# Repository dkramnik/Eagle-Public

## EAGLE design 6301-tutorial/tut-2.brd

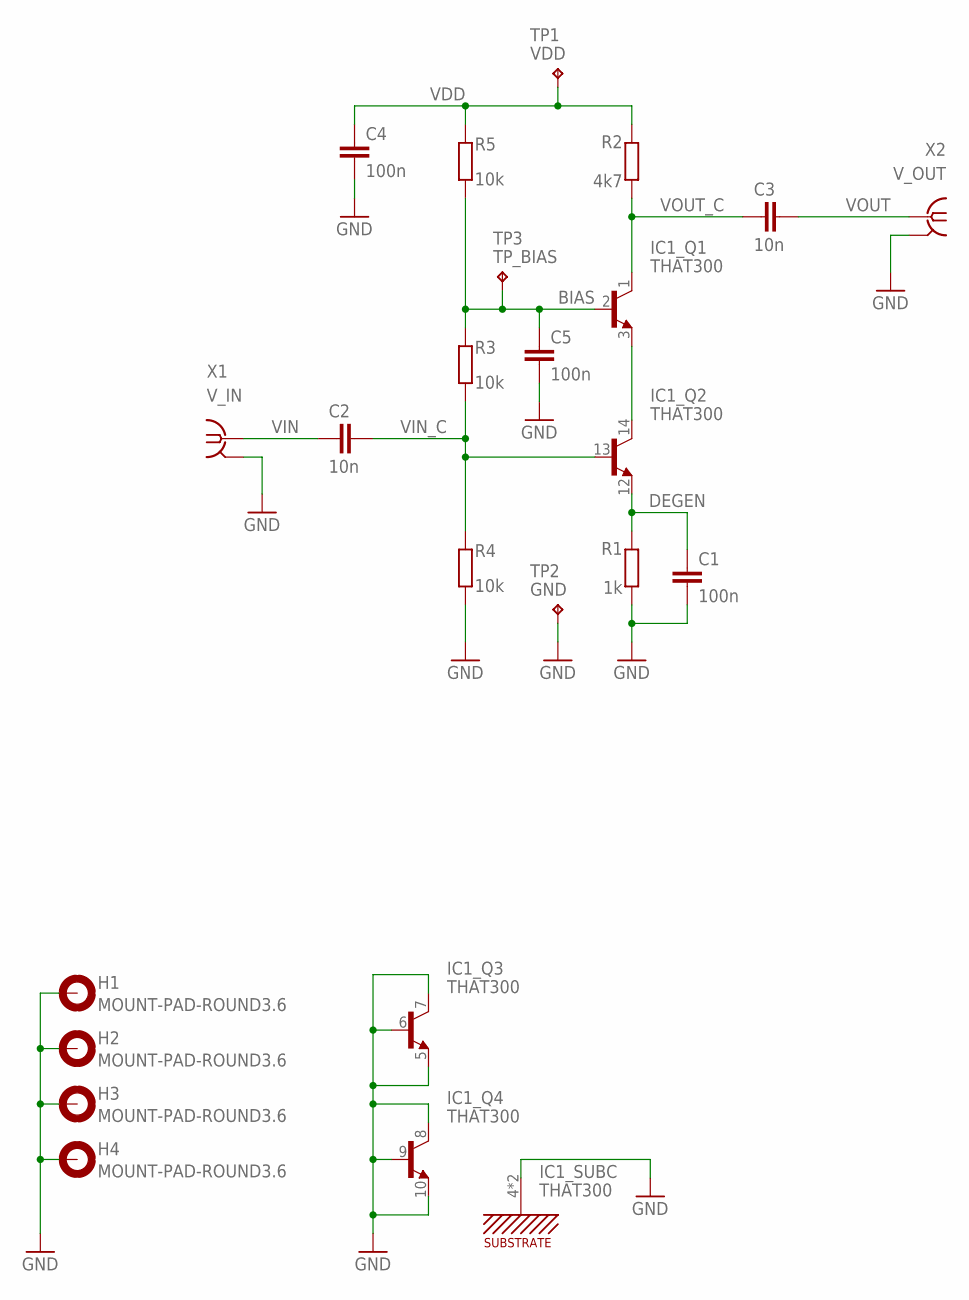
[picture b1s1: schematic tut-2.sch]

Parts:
C1, C4, C5: 100n; C050-025X075
C2, C3: 10n; C050-025X075
H1, H2, H3, H4: MOUNT-PAD-ROUND3.6; 3,6-PAD
IC1: THAT300; DIL14
R1: 1k; 0207/7
R2: 4k7; 0207/7
R3, R4, R5: 10k; 0207/7
TP1: VDD; KEYSTONE_5000_MINIATURE
TP2: GND; KEYSTONE_5000_MINIATURE
TP3: TP_BIAS; KEYSTONE_5000_MINIATURE
X1: V_IN; BU-SMA-H
X2: V_OUT; BU-SMA-H

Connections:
BIAS: C5.1, IC1.2 (B), R3.2, R5.1, TP3.P$1
DEGEN: C1.1, IC1.12 (E), R1.2
GND: C1.2, C4.2, C5.2, H1.B3,6, H2.B3,6, H3.B3,6, H4.B3,6, IC1.4 (SUBC), IC1.5 (E), IC1.6 (B), IC1.7 (C), IC1.8 (C), IC1.9 (B), IC1.10 (E), IC1.11 (SUBC), R1.1, R4.1, TP2.P$1, X1.2, X1.3 (2), X1.4 (2), X1.5 (2), X2.2, X2.3 (2), X2.4 (2), X2.5 (2)
unnamed: IC1.3 (E), IC1.14 (C)
VDD: C4.1, R2.2, R5.2, TP1.P$1
VIN: C2.1, X1.1
VIN_C: C2.2, IC1.13 (B), R3.1, R4.2
VOUT: C3.2, X2.1
VOUT_C: C3.1, IC1.1 (C), R2.1

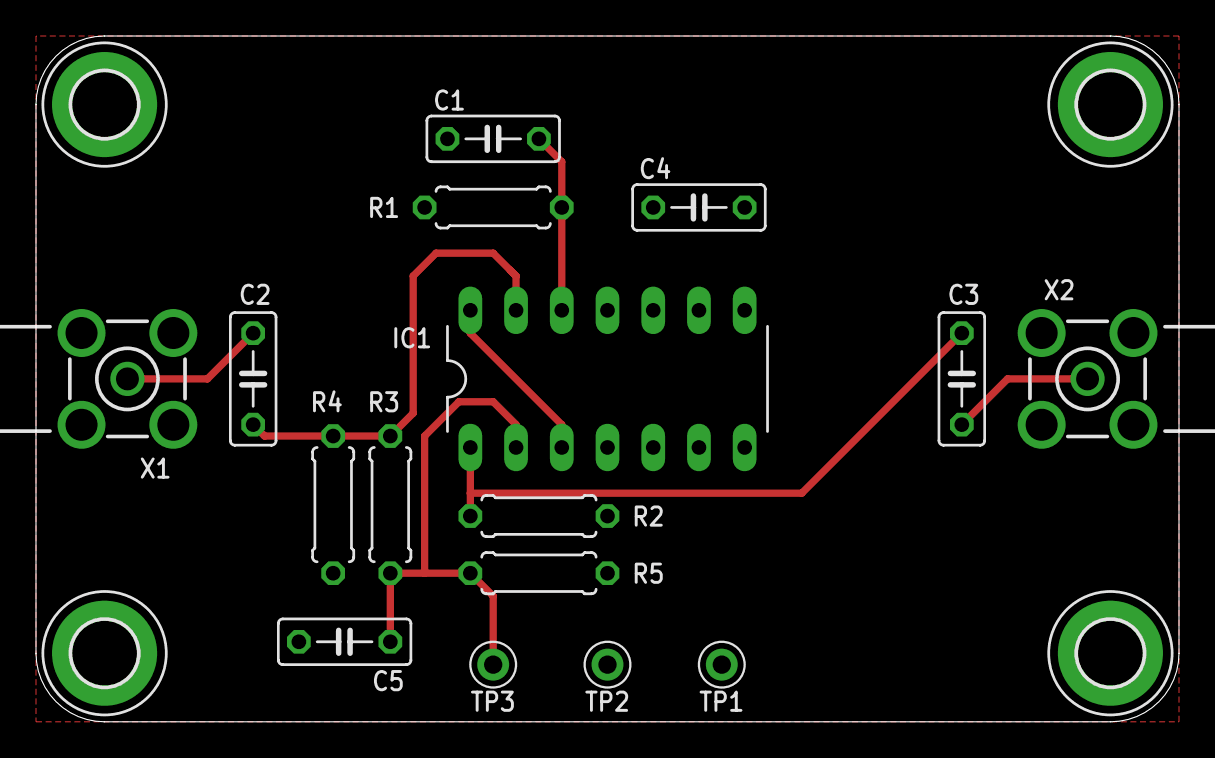
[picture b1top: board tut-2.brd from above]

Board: 2 copper layers, 63.5 x 38.1 mm, 20 parts (0 on the bottom side), 9 nets.

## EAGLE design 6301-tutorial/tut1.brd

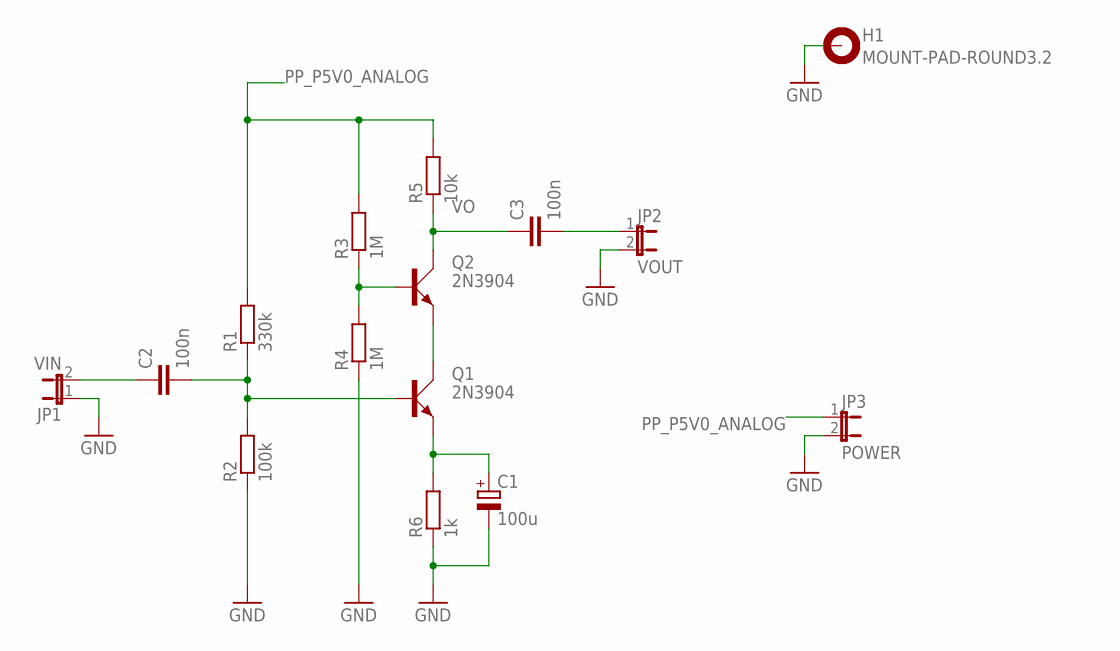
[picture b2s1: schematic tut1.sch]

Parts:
C1: 100u; E5-10,5
C2, C3: 100n; C050-025X075
H1: MOUNT-PAD-ROUND3.2; 3,2-PAD
JP1: VIN; JP1
JP2: VOUT; JP1
JP3: POWER; JP1
Q1, Q2: 2N3904; TO92D
R1: 330k; 0207/10
R2: 100k; 0207/10
R3, R4: 1M; 0207/10
R5: 10k; 0207/10
R6: 1k; 0207/10

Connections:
GND: C1.-, H1.B3,2, JP1.1, JP2.2, JP3.2, R2.1, R4.1, R6.1
unnamed: Q1.C, Q2.E
unnamed: C1.+, Q1.E, R6.2
unnamed: Q2.B, R3.1, R4.2
unnamed: C2.2, Q1.B, R1.1, R2.2
unnamed: C2.1, JP1.2
unnamed: C3.2, JP2.1
PP_P5V0_ANALOG: JP3.1, R1.2, R3.2, R5.2
VO: C3.1, Q2.C, R5.1

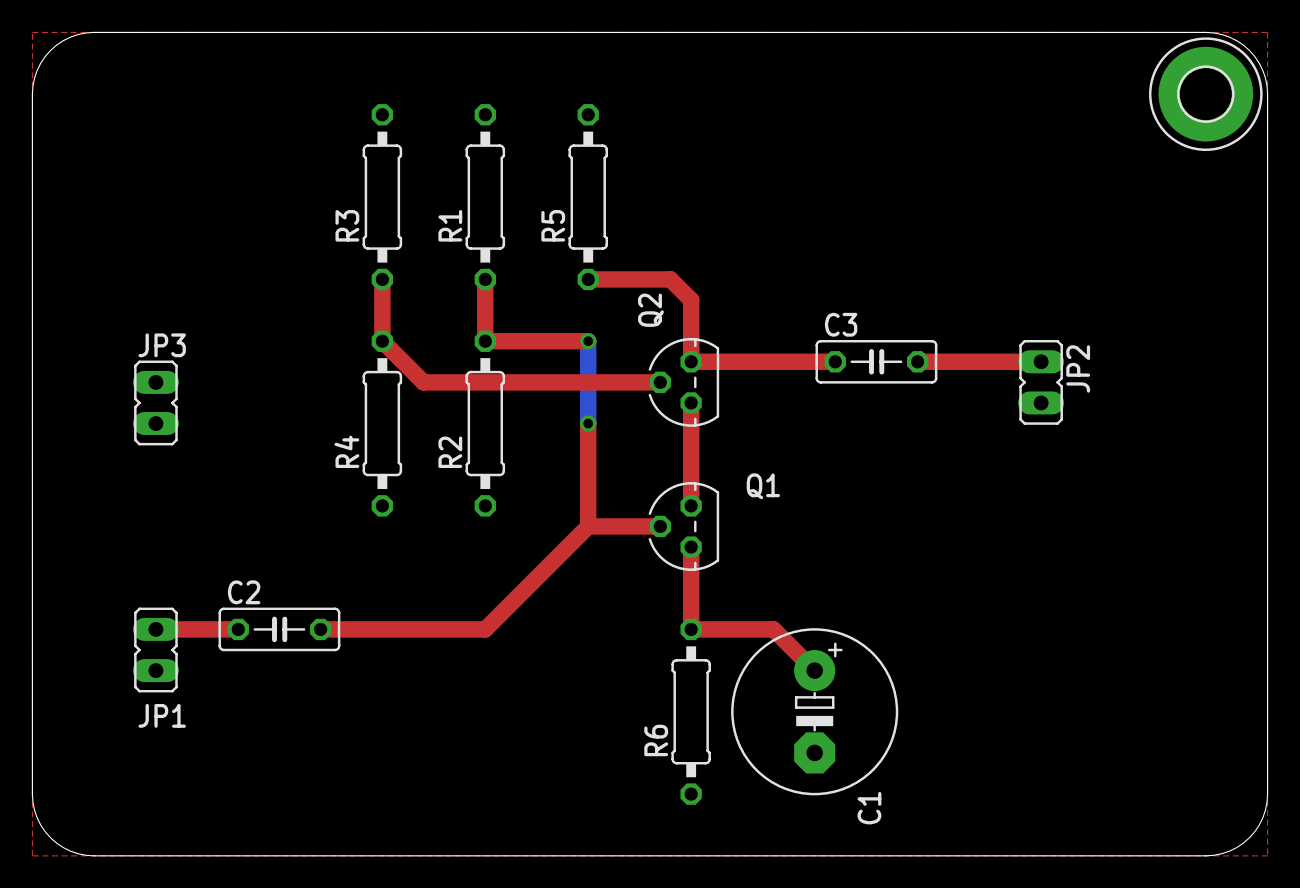
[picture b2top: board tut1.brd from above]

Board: 2 copper layers, 76.2 x 50.8 mm, 15 parts (0 on the bottom side), 9 nets.

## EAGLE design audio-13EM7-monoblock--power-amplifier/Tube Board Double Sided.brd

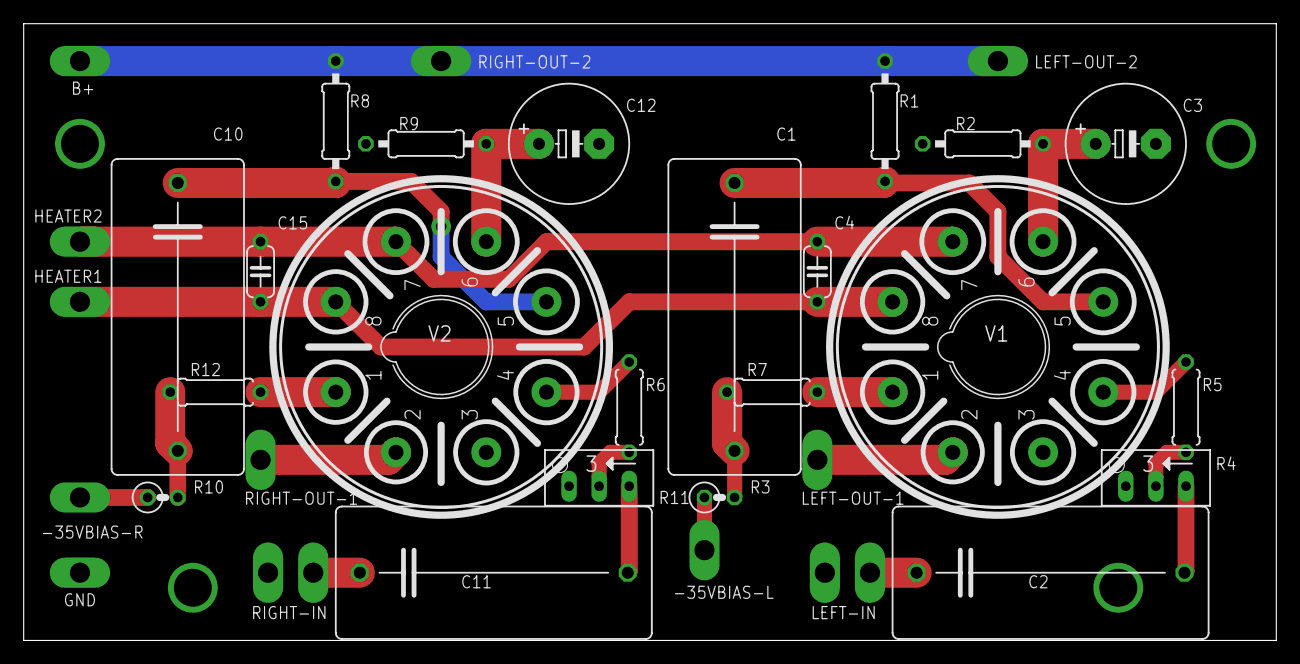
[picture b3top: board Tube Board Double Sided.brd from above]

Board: 2 copper layers, 105.7 x 52.0 mm, 34 parts (0 on the bottom side), 24 nets.

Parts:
-35VBIAS-L, -35VBIAS-R: PTR1PAD1-17Y; P1-17Y
B+: PTR1PAD1-17Y; P1-17Y
C1, C10: 0.015uF; C225-113X268
C2, C11: 0.1uF; C225-113X268
C3, C12: 100uF; E5-10,5
C4, C15: 1uF; C050-024X044
GND: PTR1PAD1-17Y; P1-17Y
HEATER1, HEATER2: PTR1PAD1-17Y; P1-17Y
LEFT-IN: PTR2; P2-38-17
LEFT-OUT-1, LEFT-OUT-2: PTR1PAD1-17Y; P1-17Y
R1, R8: 47K; 0207/10
R2, R9: 820R; 0207/10
R3, R10: 470K; 0207/2V
R4, R11: 100K; RJ9W
R5, R6: 33K; 0207/7
R7, R12: 2K2; 0207/7
RIGHT-IN: PTR2; P2-38-17
RIGHT-OUT-1, RIGHT-OUT-2: PTR1PAD1-17Y; P1-17Y
V1, V2: 13EM7; OKTAL

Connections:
B+: B+.TP, LEFT-OUT-2.TP, R1.2, R8.2, RIGHT-OUT-2.TP
GND: C3.-, C12.-, GND.TP, LEFT-IN.TP-2, R2.1, R4.A, R9.1, R11.A, RIGHT-IN.TP-2, V1.3, V2.3
HEATER: C4.1, C15.1, HEATER1.TP, V1.8, V2.8
unnamed: C4.2, C15.2, HEATER2.TP, V1.7, V2.7
unnamed: -35VBIAS-R.TP, R10.1
unnamed: R5.1, V1.4
unnamed: C1.1, R1.1, V1.5
unnamed: C3.+, R2.2, V1.6
unnamed: C1.2, R3.2, R7.2
unnamed: C2.2, R4.E
unnamed: R4.S, R5.2
unnamed: C2.1, LEFT-IN.TP-1
unnamed: C10.1, R8.1, V2.5
unnamed: LEFT-OUT-1.TP, V1.2
unnamed: R6.1, V2.4
unnamed: -35VBIAS-L.TP, R3.1
unnamed: R6.2, R11.S
unnamed: R7.1, V1.1
unnamed: C12.+, R9.2, V2.6
unnamed: C10.2, R10.2, R12.2
unnamed: C11.2, R11.E
unnamed: R12.1, V2.1
unnamed: C11.1, RIGHT-IN.TP-1
unnamed: RIGHT-OUT-1.TP, V2.2

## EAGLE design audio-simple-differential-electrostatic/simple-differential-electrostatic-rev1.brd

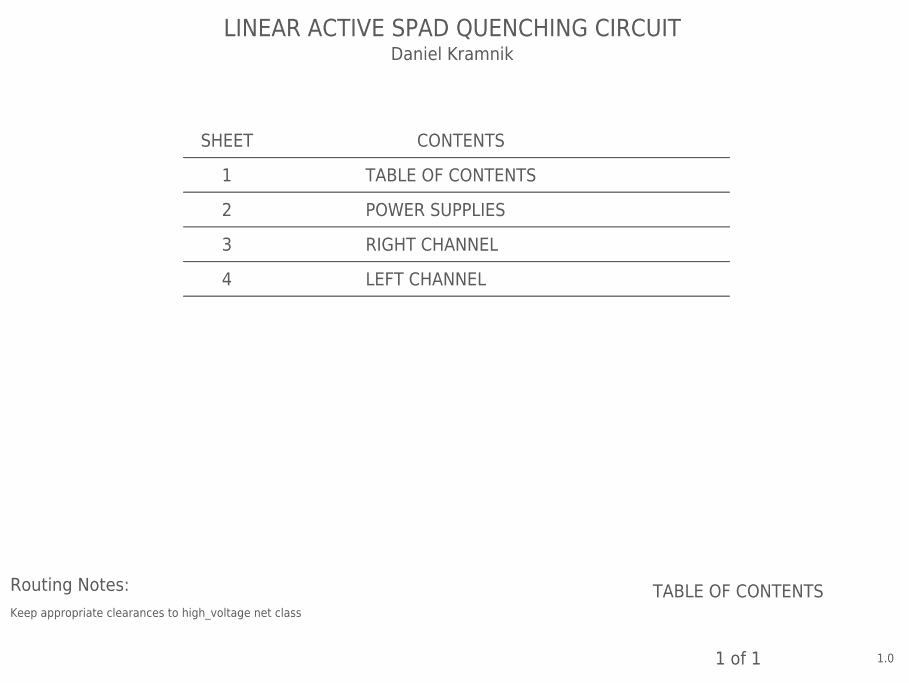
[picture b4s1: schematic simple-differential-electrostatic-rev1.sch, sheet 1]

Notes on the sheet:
TABLE OF CONTENTS
1.0
1 of 1
LINEAR ACTIVE SPAD QUENCHING CIRCUIT
SHEET
CONTENTS
Daniel Kramnik
POWER SUPPLIES
RIGHT CHANNEL
LEFT CHANNEL
Routing Notes:
Keep appropriate clearances to high_voltage net class

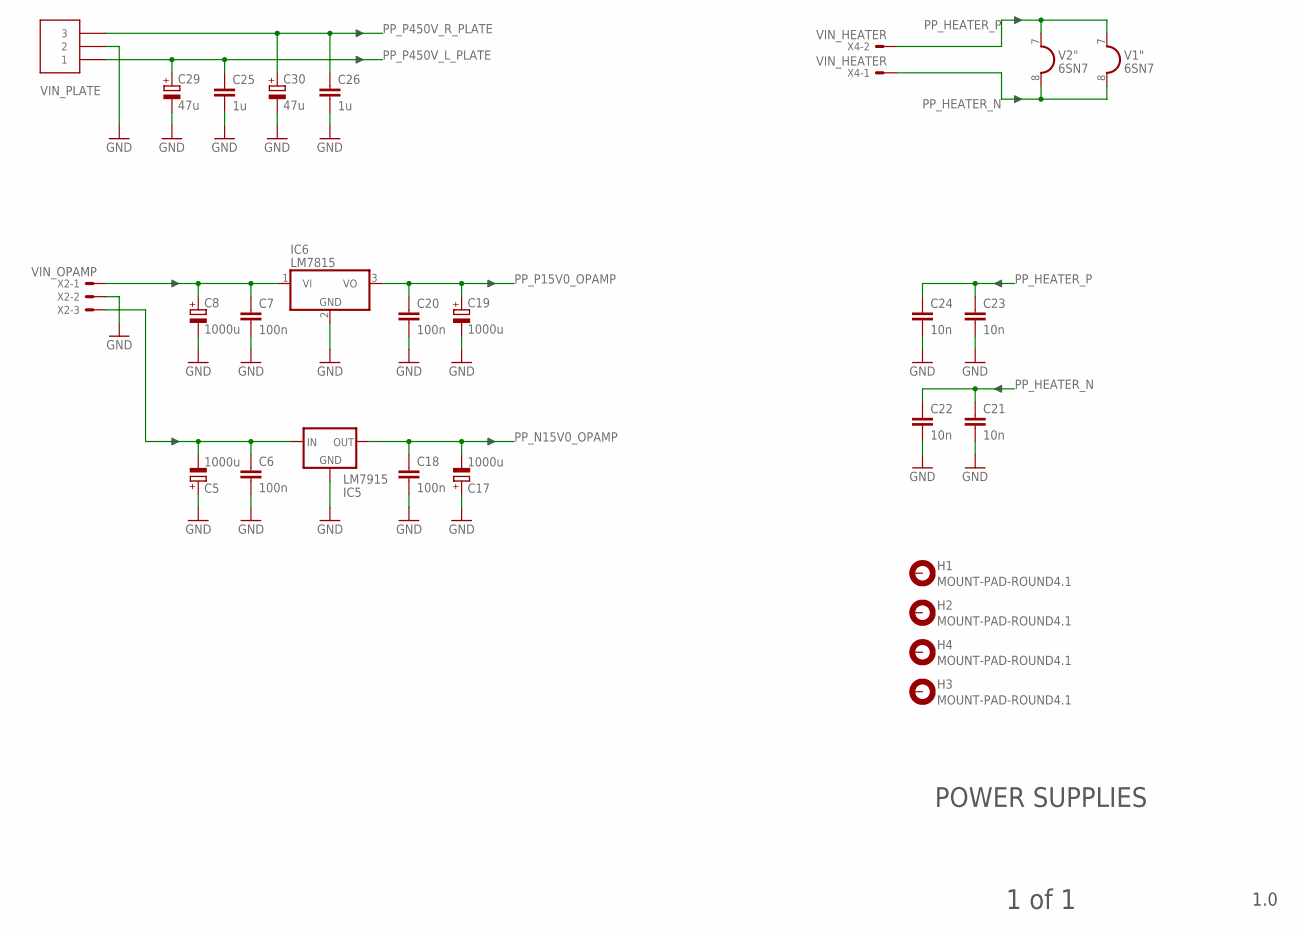
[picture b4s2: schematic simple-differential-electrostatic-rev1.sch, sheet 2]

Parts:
C5, C8, C17, C19: 1000u; E5-10,5
C6, C7, C18, C20: 100n; C050-025X075
C21, C22, C23, C24: 10n; C050-025X075
C25, C26: 1u; C325-137X374
C29, C30: 47u; EB22,5D
H1, H2, H3, H4: MOUNT-PAD-ROUND4.1; 4,1-PAD
IC5: LM7915; 79XXS
IC6: LM7815; TO220V
J2: VIN_PLATE; CONN_MOLEX_3PIN_MINI-FIT_JR
V1, V2: 6SN7; OKTAL
X2: VIN_OPAMP; KK-156-3
X4: VIN_HEATER; KK-156-2

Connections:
GND: C5.+, C6.2, C7.2, C8.-, C17.+, C18.2, C19.-, C20.2, C21.2, C22.2, C23.2, C24.2, C25.2, C26.2, C29.-, C30.-, IC5.GND, IC6.2 (GND), J2.2, X2.2; also elsewhere on the board
unnamed: C5.-, C6.1, IC5.IN, X2.3
unnamed: C7.1, C8.+, IC6.1 (VI), X2.1
PP_HEATER_N: C21.1, C22.1, V1.8 (H2), V2.8 (H2), X4.1
PP_HEATER_P: C23.1, C24.1, V1.7 (H1), V2.7 (H1), X4.2
PP_N15V0_OPAMP: C17.-, C18.1, IC5.OUT; also elsewhere on the board
PP_P15V0_OPAMP: C19.+, C20.1, IC6.3 (VO); also elsewhere on the board
PP_P450V_L_PLATE: C25.1, C29.+, J2.1; also elsewhere on the board
PP_P450V_R_PLATE: C26.1, C30.+, J2.3; also elsewhere on the board

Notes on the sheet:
POWER SUPPLIES
1.0
1 of 1

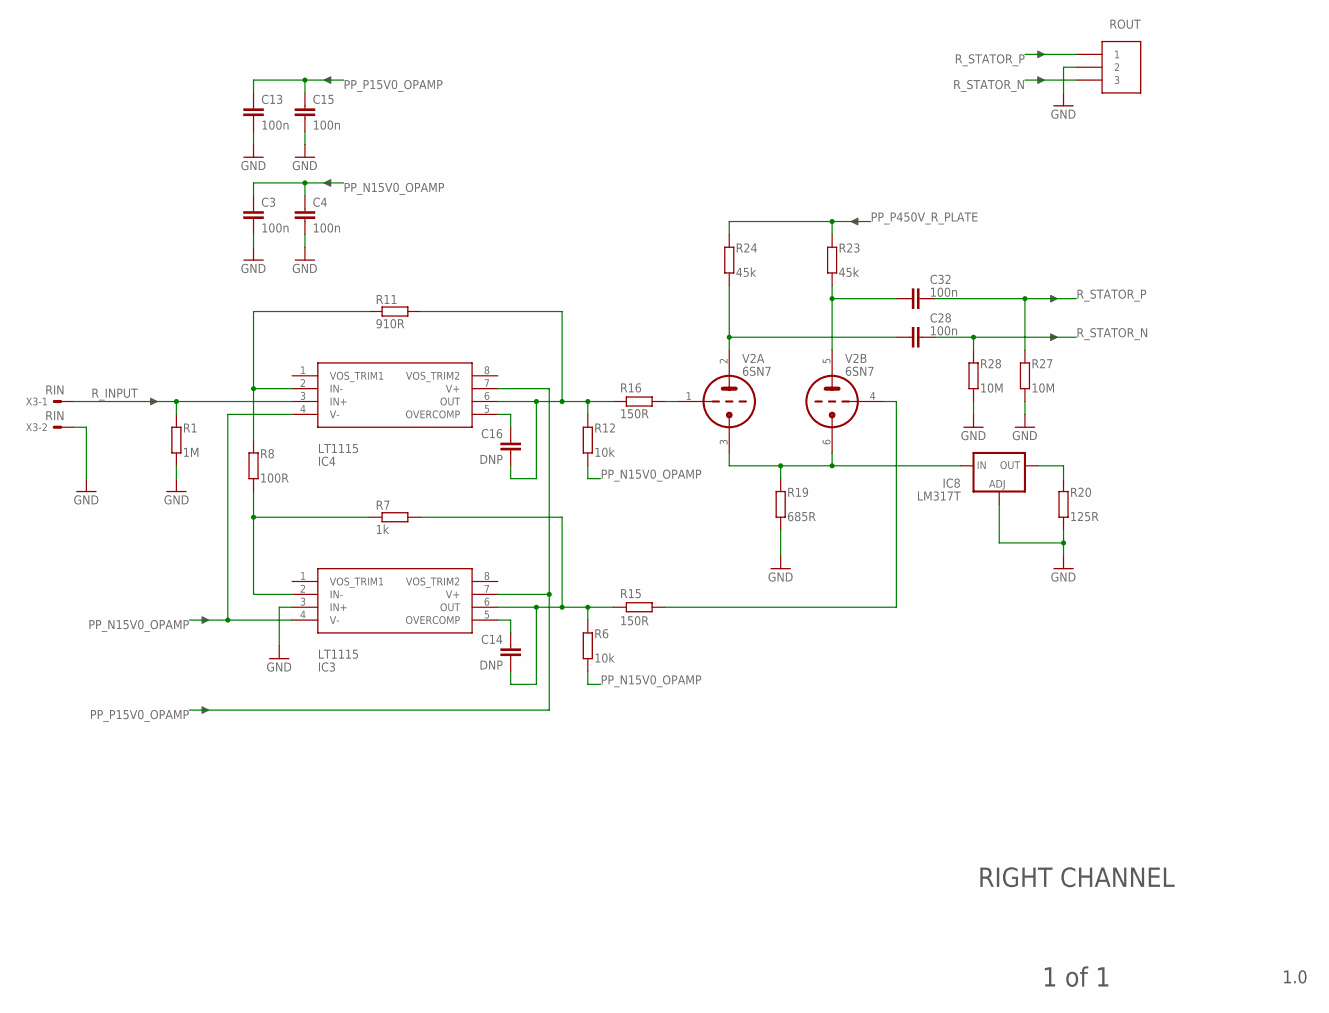
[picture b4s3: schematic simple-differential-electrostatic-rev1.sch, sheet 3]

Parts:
C3, C4, C13, C15: 100n; C050-025X075
C14, C16: DNP; C050-025X075
C28, C32: 100n; C375-155X418
IC3, IC4: LT1115; DIL08
IC8: LM317T; 317TS
J3: ROUT; CONN_MOLEX_3PIN_MINI-FIT_JR
R1: 1M; 0309/10
R6, R12: 10k; 0309/10
R7: 1k; 0309/10
R8: 100R; 0309/10
R11: 910R; 0309/10
R15, R16: 150R; 0309/10
R19: 685R; 0309/10
R20: 125R; 0309/10
R23, R24: 45k; P0613/15
R27, R28: 10M; 0309/10
V2: 6SN7; OKTAL
X3: RIN; KK-156-2

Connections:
GND: C3.2, C4.2, C13.2, C15.2, IC3.3 (IN+), IC8.1 (ADJ), J3.2, R1.1, R19.1, R20.1, R27.1, R28.1, X3.2; also elsewhere on the board
unnamed: IC8.3 (IN), R19.2, V2.3 (TK), V2.6 (TK)
unnamed: C28.1, R24.1, V2.2 (TA)
unnamed: C32.1, R23.1, V2.5 (TA)
unnamed: C16.2, IC4.6 (OUT), R11.2, R12.2, R16.2
unnamed: R15.1, V2.4 (TG)
unnamed: R16.1, V2.1 (TG)
unnamed: IC4.2 (IN-), R8.1, R11.1
unnamed: IC3.2 (IN-), R7.1, R8.2
unnamed: C14.2, IC3.6 (OUT), R6.2, R7.2, R15.2
unnamed: IC8.2 (OUT), R20.2
unnamed: C16.1, IC4.5 (OVERCOMP)
unnamed: C14.1, IC3.5 (OVERCOMP)
PP_N15V0_OPAMP: C3.1, C4.1, IC3.4 (V-), IC4.4 (V-), R6.1, R12.1; also elsewhere on the board
PP_P15V0_OPAMP: C13.1, C15.1, IC3.7 (V+), IC4.7 (V+); also elsewhere on the board
PP_P450V_R_PLATE: R23.2, R24.2; also elsewhere on the board
R_INPUT: IC4.3 (IN+), R1.2, X3.1
R_STATOR_N: C28.2, J3.3, R28.2
R_STATOR_P: C32.2, J3.1, R27.2

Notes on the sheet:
RIGHT CHANNEL
1.0
1 of 1

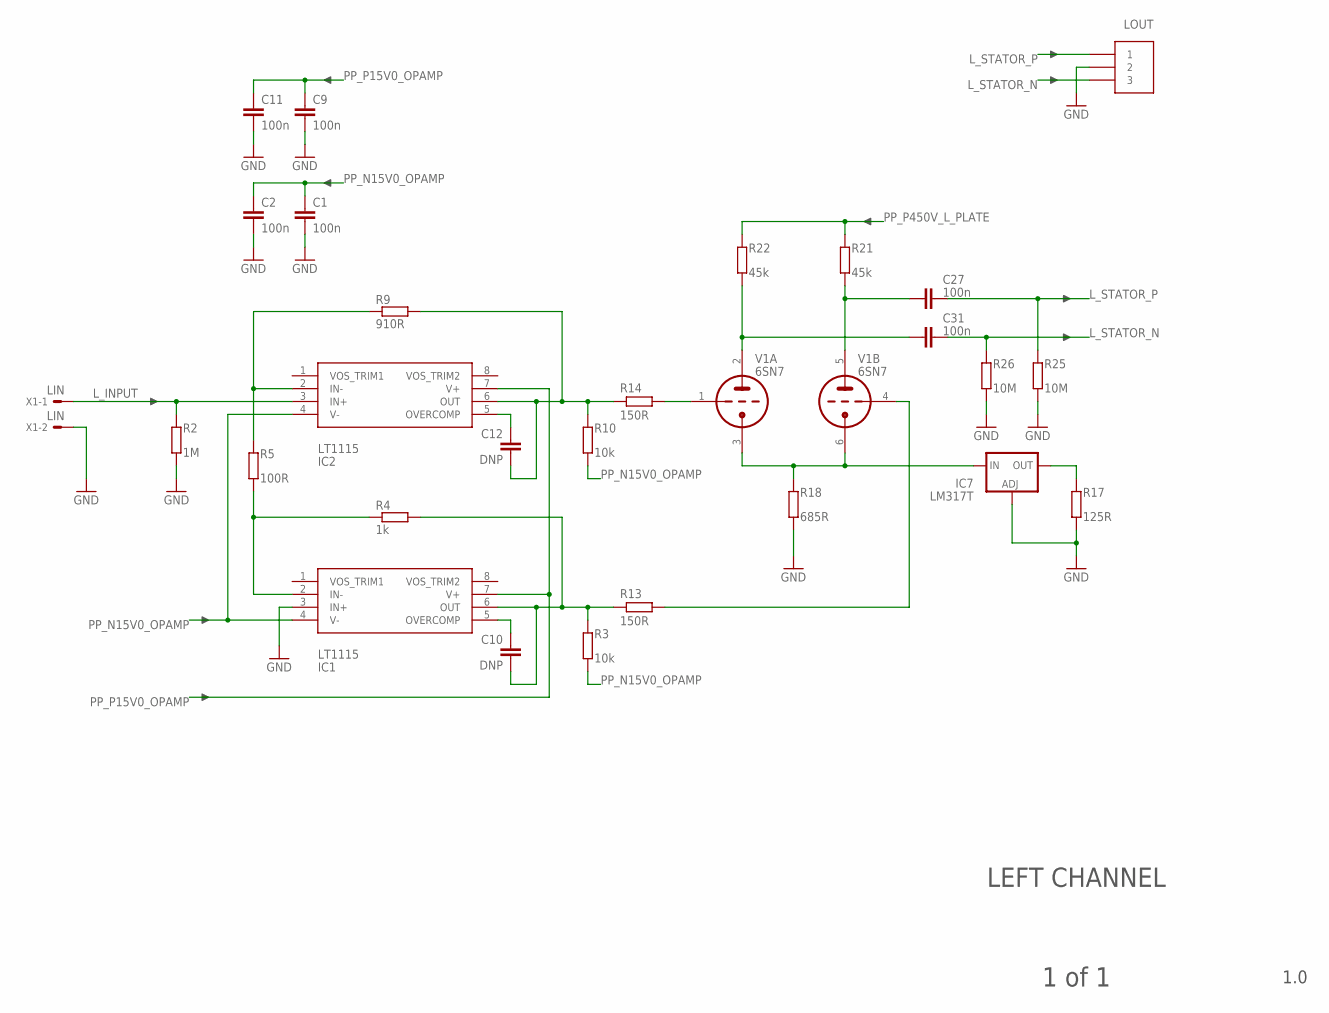
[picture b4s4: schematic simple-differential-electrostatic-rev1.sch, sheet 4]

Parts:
C1, C2, C9, C11: 100n; C050-025X075
C10, C12: DNP; C050-025X075
C27, C31: 100n; C375-155X418
IC1, IC2: LT1115; DIL08
IC7: LM317T; 317TS
J1: LOUT; CONN_MOLEX_3PIN_MINI-FIT_JR
R2: 1M; 0309/10
R3, R10: 10k; 0309/10
R4: 1k; 0309/10
R5: 100R; 0309/10
R9: 910R; 0309/10
R13, R14: 150R; 0309/10
R17: 125R; 0309/10
R18: 685R; 0309/10
R21, R22: 45k; P0613/15
R25, R26: 10M; 0309/10
V1: 6SN7; OKTAL
X1: LIN; KK-156-2

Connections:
GND: C1.2, C2.2, C9.2, C11.2, IC1.3 (IN+), IC7.1 (ADJ), J1.2, R2.1, R17.1, R18.1, R25.1, R26.1, X1.2; also elsewhere on the board
L_INPUT: IC2.3 (IN+), R2.2, X1.1
L_STATOR_N: C31.2, J1.3, R26.2
L_STATOR_P: C27.2, J1.1, R25.2
unnamed: IC7.3 (IN), R18.2, V1.3 (TK), V1.6 (TK)
unnamed: C31.1, R22.1, V1.2 (TA)
unnamed: C27.1, R21.1, V1.5 (TA)
unnamed: R13.1, V1.4 (TG)
unnamed: R14.1, V1.1 (TG)
unnamed: C12.2, IC2.6 (OUT), R9.2, R10.2, R14.2
unnamed: IC2.2 (IN-), R5.1, R9.1
unnamed: IC1.2 (IN-), R4.1, R5.2
unnamed: C10.2, IC1.6 (OUT), R3.2, R4.2, R13.2
unnamed: C12.1, IC2.5 (OVERCOMP)
unnamed: C10.1, IC1.5 (OVERCOMP)
unnamed: IC7.2 (OUT), R17.2
PP_N15V0_OPAMP: C1.1, C2.1, IC1.4 (V-), IC2.4 (V-), R3.1, R10.1; also elsewhere on the board
PP_P15V0_OPAMP: C9.1, C11.1, IC1.7 (V+), IC2.7 (V+); also elsewhere on the board
PP_P450V_L_PLATE: R21.2, R22.2; also elsewhere on the board

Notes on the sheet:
LEFT CHANNEL
1.0
1 of 1

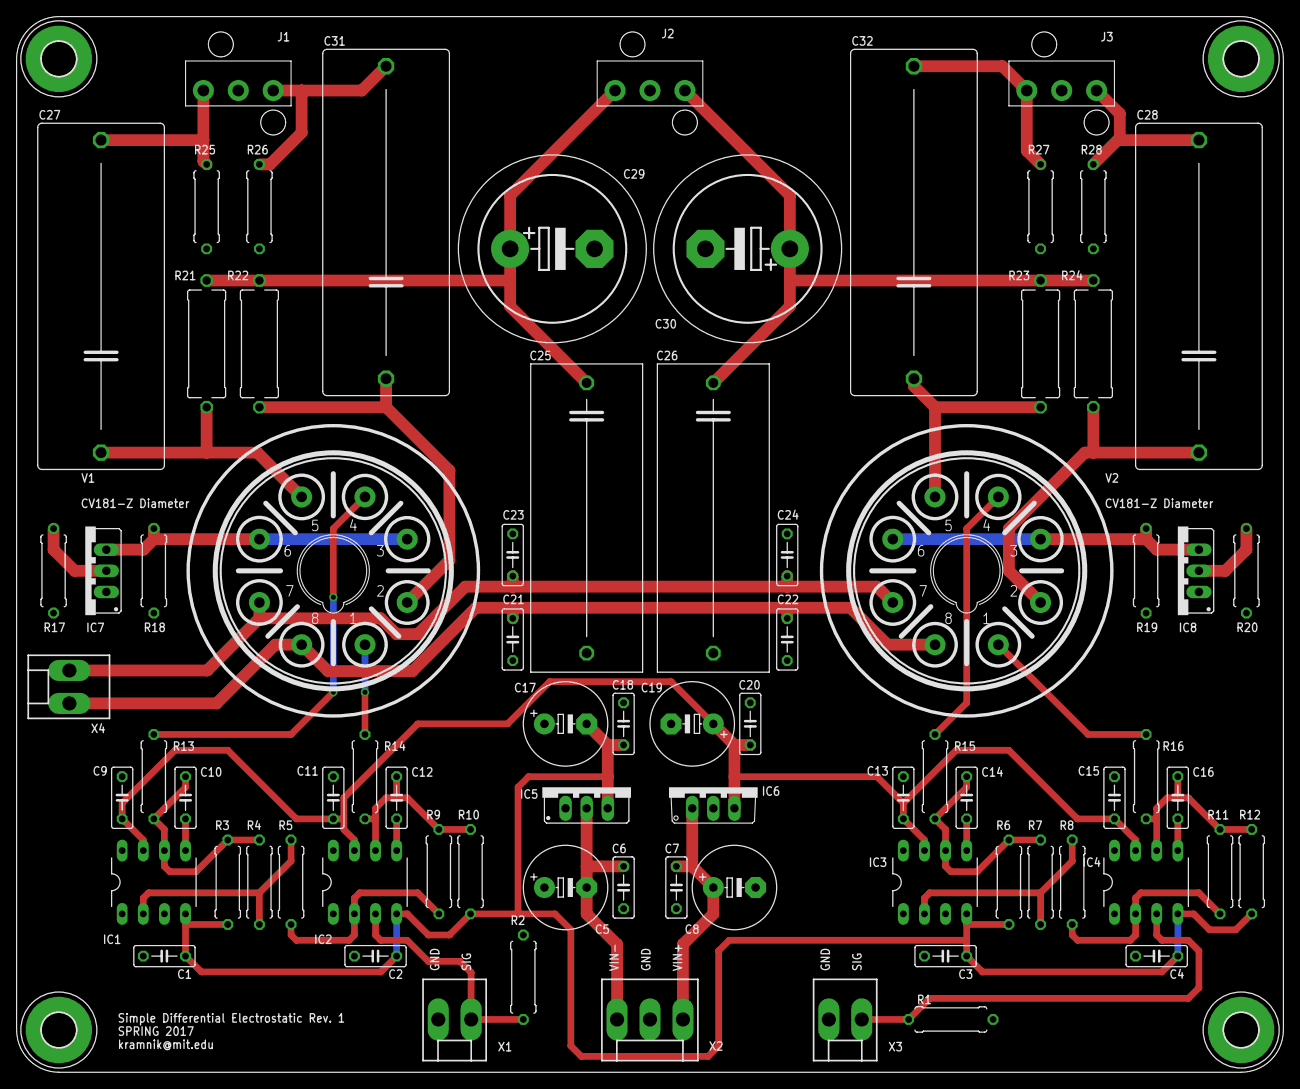
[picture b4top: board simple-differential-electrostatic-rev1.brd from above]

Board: 2 copper layers, 152.4 x 127.0 mm, 81 parts (0 on the bottom side), 39 nets.
